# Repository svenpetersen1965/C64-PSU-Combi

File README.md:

# C64-PSU-Combi
A PSU for the Commodore C64 and up to two 1541-II floppy disk drives. It is based on a transformer 
for the 9VAC, which is required in a C64 and a (PCB) external power supply module, which provides
the +5V and +12V for the C64 and the 1541-II floppy disk drives. Depending on the used power supply
module, one of the 1541-II connectors can be replaced with an Amiga connection, which also requires 
-12V. This option has not been tested, since I don't have an Amiga. The PSU combi should be strong 
enough.

This build is for the more experienced, since power supplies can be hazzardous and the involved 
mains voltage is potentially lethal.

Find some info on the required cable making <a href="http://tech.guitarsite.de/cable_making.html">on my website</a>

The power supply has  an open concept and can be configured to taste. It should be planned before 
parts are purchased.

C64 PSU Combi in a Hammond 1411P case

C64 PSU Combi in a Teko 384 case

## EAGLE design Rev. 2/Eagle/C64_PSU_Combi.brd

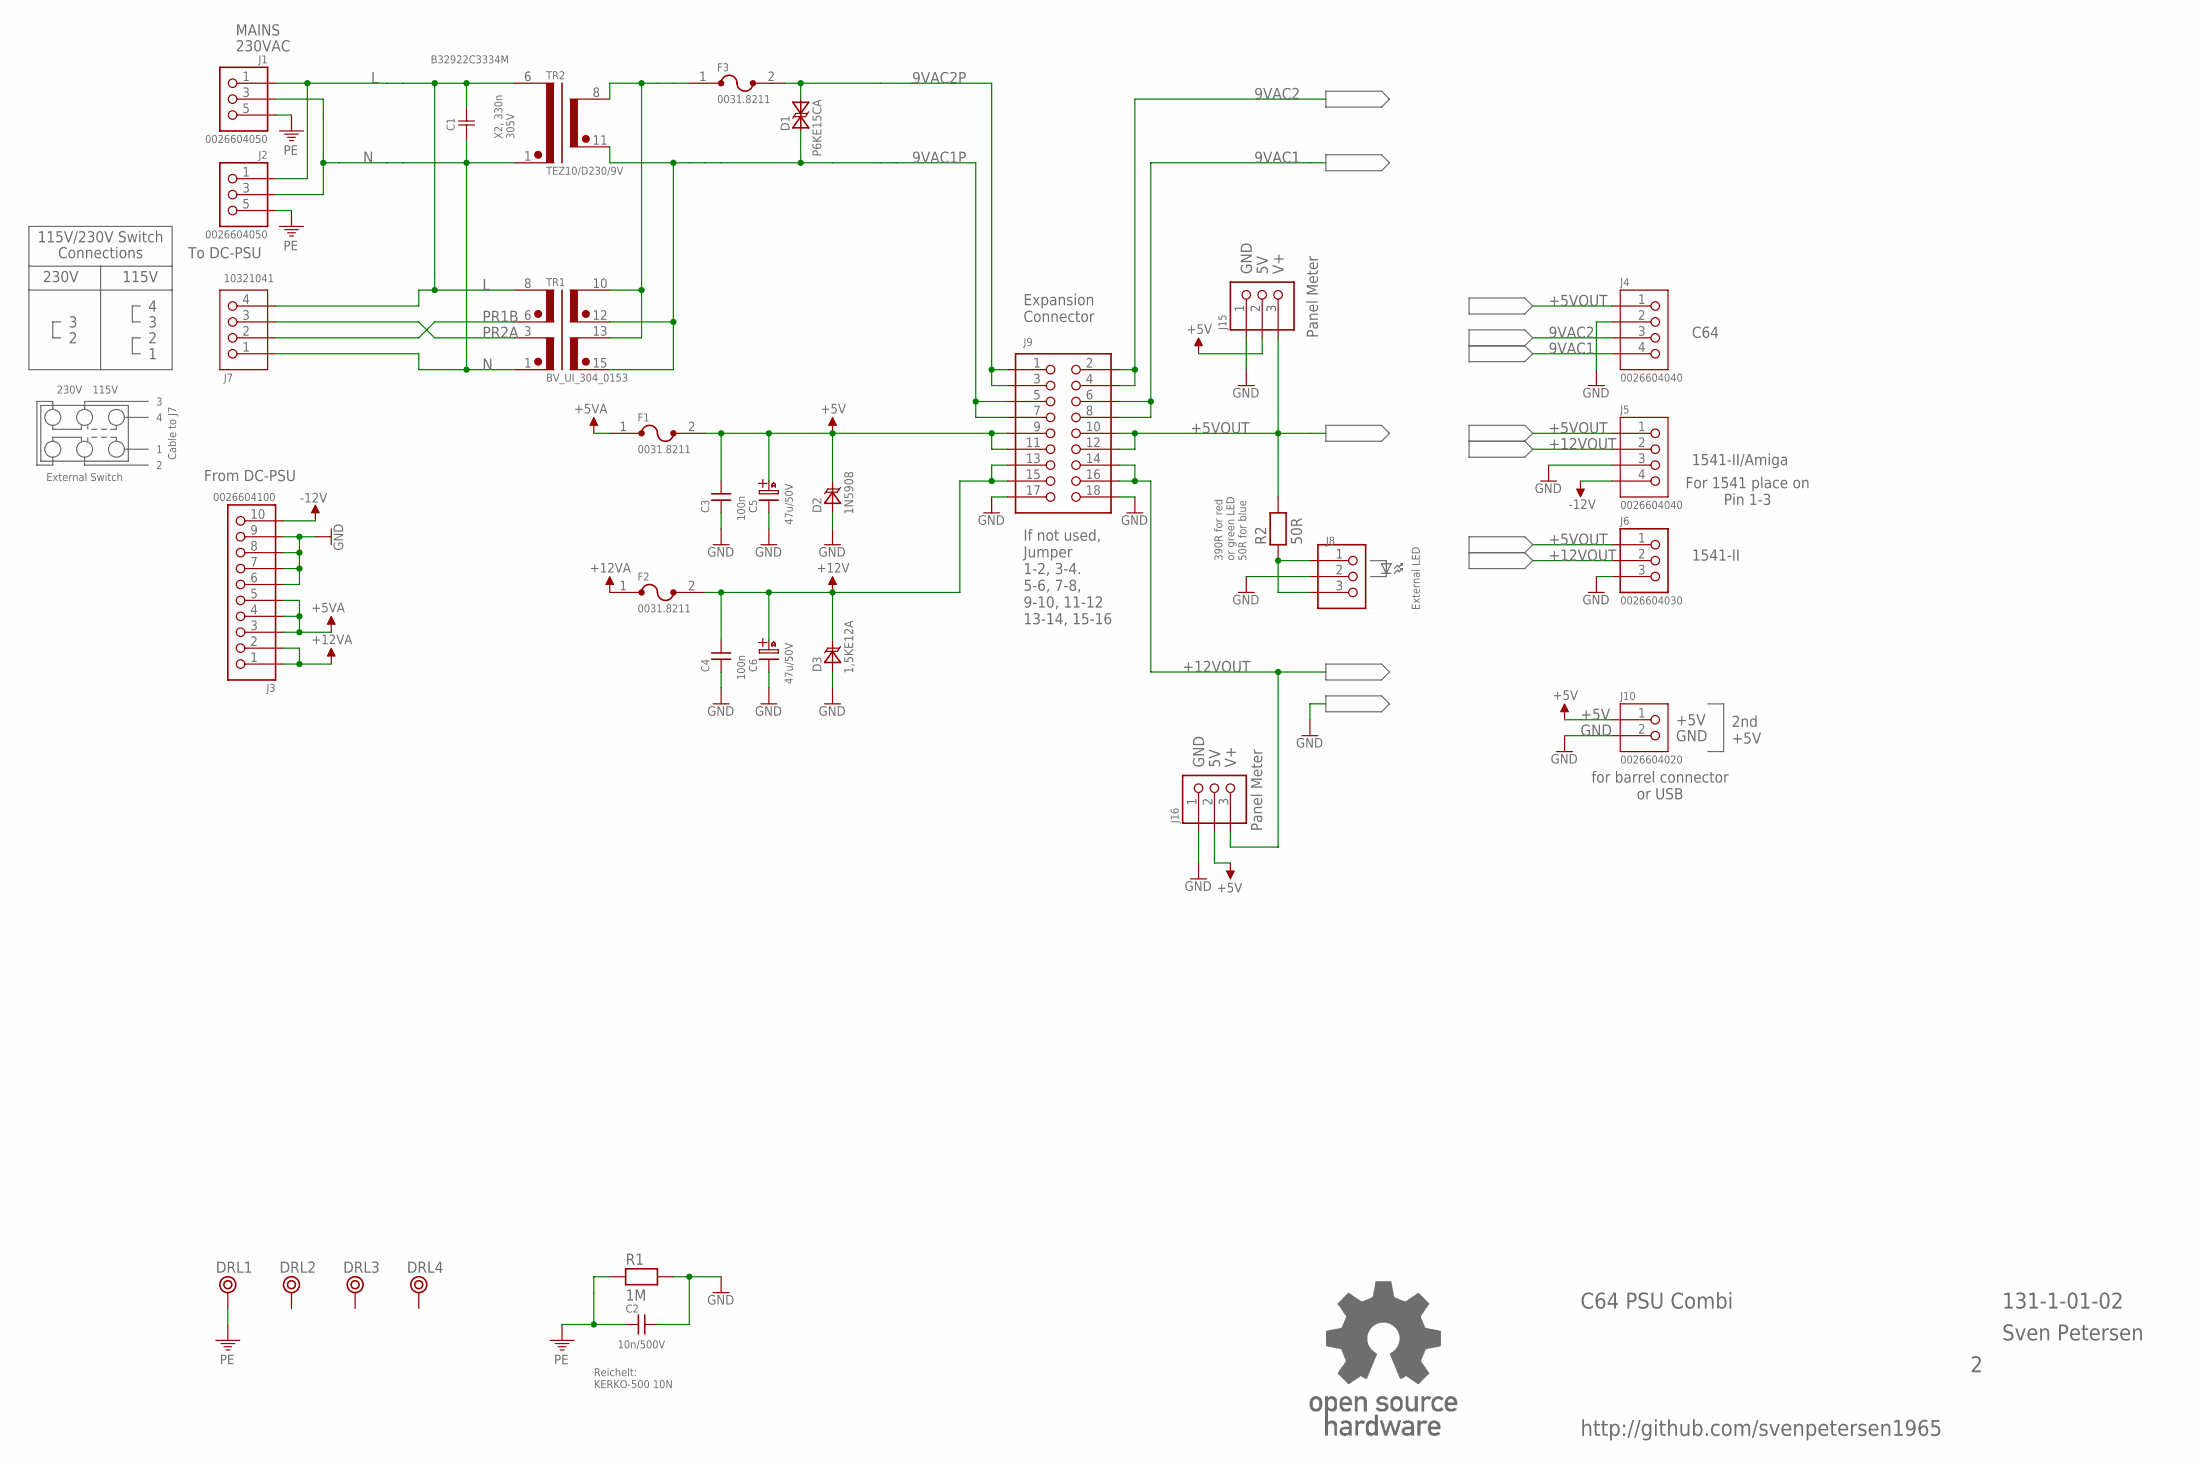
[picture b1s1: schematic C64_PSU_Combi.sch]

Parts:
C1: B32922C3334M; C-18X8-RM15
C2: 10n/500V; C-5
C3, C4: 100n; C-2,5
C5, C6: 47u/50V; C07/2,5
D1: P6KE15CA; CB417NP
D2: 1N5908; CB429
D3: 1,5KE12A; DO-201
DRL1: BOHR3,5OR; BOHR3,5_OHNE_RESTRICT
DRL2, DRL3, DRL4: BOHR3,5
F1, F2, F3: 0031.8211
J1, J2: 0026604050; SPOX_3.96_5P3
J3: 0026604100; SPOX_3.96_10P
J4, J5: 0026604040; SPOX_3.96_4P
J6: 0026604030; SPOX_3.96_3P
J7: 10321041; SPOX_5.08_4P
J8: PINHD-1X3; 1X03
J9: COMBI-9X2P; COMBI-9X2
J10: 0026604020; SPOX_3.96_2P
J15, J16: 6410-3P
R1: 1M; R-10
R2: 50R; R-10
TR1: BV_UI_304_0153; UI30
TR2: TEZ10/D230/9V; TEZ10
U$31: OPEN_SOURCE_HW; OPENHW

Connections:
9VAC1: J4.4, J9.6, J9.8
9VAC1P: D1.A (A1), J9.5, J9.7, TR1.12 (SEC1B), TR1.15 (SEC2B), TR2.11 (SEC12)
9VAC2: J4.3, J9.2, J9.4
9VAC2F: F3.1, TR1.10 (SEC1A), TR1.13 (SEC2A), TR2.8 (SEC11)
9VAC2P: D1.K (A2), F3.2, J9.1, J9.3
+5V: C3.2, C5.A (+), D2.K, F1.2, J9.9, J9.11, J10.1, J15.2, J16.2
+5VA: F1.1, J3.3, J3.4, J3.5
+5VOUT: J4.1, J5.1, J6.1, J9.10, J9.12, J15.3, R2.2
+12V: C4.2, C6.A (+), D3.K, F2.2, J9.13, J9.15
+12VA: F2.1, J3.1, J3.2
+12VOUT: J5.2, J6.2, J9.14, J9.16, J16.3
-12V: J3.10, J5.4
GND: C2.2, C3.1, C4.1, C5.K (-), C6.K (-), D2.A, D3.A, J3.6, J3.7, J3.8, J3.9, J4.2, J5.3, J6.3, J8.2, J9.17, J9.18, J10.2, J15.1, J16.1, R1.2
L: C1.2, J1.1, J2.1, J7.4, TR1.8 (PRI1A), TR2.6 (PRI1)
N: C1.1, J1.3 (2), J2.3 (2), J7.1, TR1.1 (PRI2B), TR2.1 (PRI2)
unnamed: J8.1, J8.3, R2.1
PE: C2.1, DRL1.P$1, J1.5 (3), J2.5 (3), R1.1
PR1B: J7.2, TR1.6 (PRI1B)
PR2A: J7.3, TR1.3 (PRI2A)

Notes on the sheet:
230VAC
X2, 330n 305V
External LED
390R for red or green LED 50R for blue
Reichelt: KERKO-500 10N
Expansion Connector
If not used, Jumper 1-2, 3-4. 5-6, 7-8, 9-10, 11-12 13-14, 15-16
GND
Panel Meter
MAINS
From DC-PSU
C64
1541-II/Amiga
1541-II
C64 PSU Combi
131-1-01-02
Sven Petersen
To DC-PSU
For 1541 place on Pin 1-3
115V/230V Switch
230V
115V
Connections
Cable to J7
External Switch
http://github.com/svenpetersen1965
+5V
2nd +5V
for barrel connector or USB

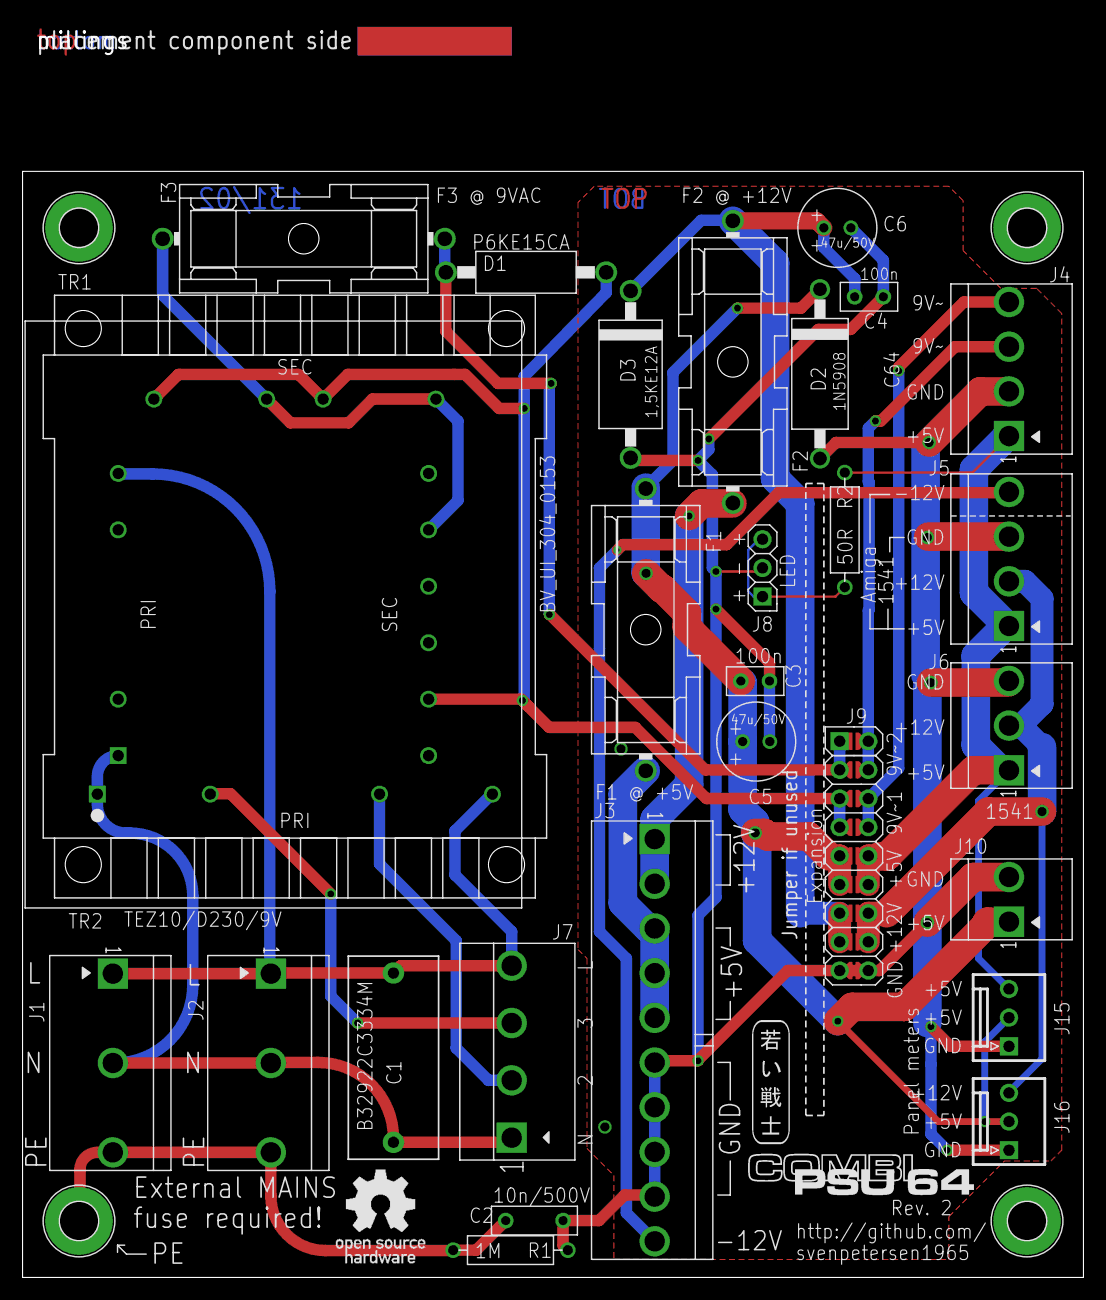
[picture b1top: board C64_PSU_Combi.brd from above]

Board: 2 copper layers, 94.0 x 111.2 mm, 37 parts (0 on the bottom side), 19 nets.

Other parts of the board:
U$43: SVEN_TAG
U$44: PCB-TITLE/
U$45: 2LAYER
U$49: COMBIPSU64

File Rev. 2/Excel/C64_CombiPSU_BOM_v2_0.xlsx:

C64 Combi PSU Rev. 2
Bill of Material Rev. 2.0
Pos. | Qty | Value | Footprint | Ref.-No. | Comment
1 | 1 | 131-2-01-02 | 2 Layer | PCB Rev. 2 | 2 layer, Cu 35µ, HASL, 94.0 x 98.0, 1.6mm FR4
2 | 2 | 22-27-2031 | 6410-3P | J15, J16 | optional (for panel meters): Molex 6410/22-27-2031 (KK, 2.54mm, 3p), e.g. Reich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
3 | 2 | 22-01-3037 |  | (J15), (J16) | crimp housing, optional (for panel meters), Molex. E.g. Reichelt: MOLEX 2201303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
4 | 6 | 08-50-0114 |  | (J15), (J16) | crimp terminal, optional (for panel meters), Molex. E.g. Reichelt: MOLEX 850011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
5 | 1 | 1x3p, 2.54mm | 1X03 | J8 | standard pin header, 2.54mm pitch
6 | 1 | dupont housing, 3p |  | (J8) | ebay, AliExpress or other
7 | 2 | dupont terminals, female |  | (J8) | ebay, AliExpress or other
8 | 1 | LED, blue |  | (J8) | Power LED, blue (R1 is calculated for blue)
9 | 1 | 2x9p, 2.54mm | 2X09 | J9 | standard pin header, 2.54mm pitch
10 | 8 | jumper, 2.54mm |  | (J9) | standard jumper (rated 3A). E.G. Reichelt: JUMPER 2,54 SW, tme.eu: 63429-202LF
11 | 2 or 1 | 26604030 | SPOX_3.96_3P | J6, (J5) | J5 for 1541 option, Molex SPOX, e.G. Reichelt: MOLEX 26604030, tme.eu: MX-26-60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
12 | 2 or 1 | 09503031 |  | (J6), (J5) | crimp housing: Molex. E.g. Reichelt: MOLEX 9503031, tme.eu: MX-2139-3A
13 | 6 or 3 | 08500106 |  | (J6), (J5) | crimp terminal, Molex. E.g. Reichelt: MOLEX 08500106, tme.eu: MX-2478-1-P913L (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
14 | 1 or 2 | 26604040 | SPOX_3.96_4P | J4, (J5) | J5 for Amiga option, Molex SPOX, e.G. Reichelt: MOLEX 26604040, tme.eu: MX-26-6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
15 | 1 or 2 | 09503041 |  | (J4), (J5) | crimp housing: Molex. E.g. Reichelt: MOLEX 9503041, tme.eu: MX-2139-4A
16 | 4 or 8 | 08500106 |  | (J4), (J5) | crimp terminal, Molex. E.g. Reichelt: MOLEX 08500106, tme.eu: MX-2478-1-P913L (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
17 | 2 | 26604050 | SPOX_3.96_5P3 | J1, J2 | Modification: Remove Pin 2 and Pin 4. Molex SPOX, e.G. Reichelt: MOLEX 26604050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
18 | 2 | 09503051 |  | (J1), (J2) | crimp housing: Molex. E.g. Reichelt: MOLEX 9503051, tme.eu: MX-2139-5A
19 | 6 | 08500106 |  | (J1), (J2) | crimp terminal, Molex. E.g. Reichelt: MOLEX 08500106, tme.eu: MX-2478-1-P913L (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
20 | 1 | 26604100 | SPOX_3.96_10P | J3 | Molex SPOX, e.G. Reichelt: MOLEX 26604100, tme.eu: MX-26-60-4100
21 | 1 | 09503101 |  | (J3) | crimp housing: Molex. E.g. Reichelt: MOLEX 9503101, tme.eu: MX-2139-10A
22 | 10 | 08500106 |  | (J3) | crimp terminal, Molex. E.g. Reichelt: MOLEX 08500106, tme.eu: MX-2478-1-P913L (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
23 | 3 | 0031.8211 | 318211 | F1, F2, F3 | Schurter fuse holder (5x20mm). E.g. Reichelt: PL OGN-25, tme.eu: 0031.8211
24 | 1 | 3AT, 5x20mm |  | (F1) | fuse, refer to documentation
25 | 1 | 1.6AT, 5x20mm |  | (F2) | fuse, refer to documentation
26 | 1 | 1.6AT, 5x20mm |  | (F3) | fuse, refer to documentation
27 | 1 | 1,5KE12A | DO-201 | D3 | 12V TVS diode. E.g. ST Micro. E.g. Reichelt: 1,5KE 12A, tme.eu: 1.5KE12A
28 | 2 | 100n | C-2,5 | C3, C4 | Ceramic Cap, 50V, pitch 2.5mm
29 | 1 | 10n/500V | C-5 | C2 | Ceramic Cap, 500V, pitch 5mm, Reichelt: KERKO-500 10N, tme.eu: CCH-10K (=10 pac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
30 | 1 | 1M | R-10 | R1 | Resistor, metal film, 5% or better, 0,6W
31 | 1 | 1N5908 | CB429 | D2 | 5V TVS diode. ST Micro. E.g. Reichelt: 1N 5908, tme.eu: 1N5908
32 | 2 | 47u/50V | C07/2,5 | C5, C6 | el. cap., diameter 7mm, pitch 2.5mm, 105°C, e.G. Reichelt: EB-A 47U 50, tme.eu: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
33 | 1 | 50R | R-10 | R2 | Resistor, metal film, 5% or better, 0,6W, calculated for blue led. For red, gre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
34 | 1 | B32922C3334M | C-18X8-RM15 | C1 | X2-capacitor, 330n, 305V, EPCOS. E.g. Reichelt EPCO B32922C3334, tme.eu: B32922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
35 | 1 | P6KE15CA | CB417NP | D1 | 15V bi-dir TVS diode, ST Micro, e.G. Reichelt: P6KE 15CA, tme.eu: P6KE15CA
36 | 1 | TEZ10/D230/9V | TEZ10 | TR2 | BREVE TUFVASSONS transformer, option 230V only, tme.eu: TEZ10/D/9V
37 | 1 | BV UI 304 0153 | UI30 | TR1 | Hahn transformer, option 115V/230V, tme.eu: BVUI3040153
38 | 1 | 10321041 | SPOX_5.08_4P | J2 | MOLEX, option: 115V/230V switch, tme.eu: MX-5281-04A
39 | 1 | 10013046 |  | (J2) | MOLEX, option: 115V/230V switch., tme.eu: MX-5197-04, Farnell: 2612656 , Mouser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
40 | 4 | 08701031 |  | (J2) | Molex Crimp terminal, option 115V/230V, Farnell: 2060658, rs-online.com: 670-62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
41 | 1 | T22205B436B |  | (J2) | Bulgin, option 115/230V (switch), tme.eu: AE-T22205B
42 | 123cm | AWG21/0.5mm², red |  |  | Cable
43 | 90cm | AWG21/0.5mm², yellow |  |  | Cable
44 | 128cm | AWG21/0.5mm², black |  |  | Cable
45 | 64cm | AWG21/0.5mm², green |  |  | Cable
46 | 56cm | AWG21/0.5mm², blue |  |  | Cable
47 | 56cm | AWG21/0.5mm², brown |  |  | Cable
48 | 34cm | AWG21/0.5mm², green/yellow |  |  | Cable
49 | 10cm | AWG24/0.25mm², red |  |  | Cable
50 | 10cm | AWG24/0.25mm², black |  |  | Cable
49 | 3cm | 2.4/1.2mm |  |  | shrinkable sleve, shrink ration 1:2
50 | 24cm | 3.2/1.6mm |  |  | shrinkable sleve, shrink ration 1:2
50 | 7 | FastOn 6.3x0.8, full iso, red |  |  | crimp connector, e.g. tme.eu 2-520183-2
51 | 7 | Fork connectors, M3, iso, red |  |  | crimp connector, e.g. tme.eu ST-090/R
52 | 1 | DIN jack, 7-way, panel mount |  |  | e.b. tme.eu: DC-109
53 | 2 | DIN jack, 4-way, panel mount |  |  | e.g. tme.eu: MAB4
54 | 1 | Hammond 1411P |  |  | Aluminum case, tme.eu: HM-1411P
55 | 1 | Mounting plate |  |  | Aluminum sheet (99mm x 97mm x 2mm), see drawing: Doc. No. 131-3-01-01
56 | 75mm | 10mm/20mm x 1.5mm |  |  | Aluminum angle profile, see drawing: Doc. No. 131-3-01-01
57 | 8 | M3x10, countersunk |  |  | Screw, DIN 965
58 | 18 | M3, selflocking nut |  |  | DIN 985
59 | 9 | M3, toothed washer |  |  | DIN 6798
60 | 4 | M3/15mm, male/female |  |  | spacer
61 | 10 | M3x10 |  |  | DIN 7985
62 | 10 | M3 washer (3.2mm) |  |  | DIN 125A
63 | 2 | M3x6 |  |  | DIN 7985
64 | 22 | W2.5/L100 |  |  | Cable tie, width 2.5mm, length 100mm, e.g. tme.eu: BMB1025
65 | 1 | RD-50A |  |  | Mean Well DC PSU, e.g. tme.eu: RD-50A
66 | 2 | DIN plugs, 7-way |  |  | e.g. tme.eu MAS70SGR
67 | 4 | DIN plugs, 4 way |  |  | e.g. tme.eu: MAS40
68 | 3.9m | 4xAWG21/0.5mm² |  |  | Cable
69 | 1 | adhesive socket |  |  | for cable ties/cabeling
70 | 1 | 6200.2300 |  |  | Marquardt, appliance connector, tme.eu: 6200.6300
71 | 1 | 1835.3118 |  |  | Marquardt, illuminated mains switch, tme.eu: 1835.3118
72 | 1 | 0026604020 | SPOX_3.96_2P | J10 | Molex KK 396 Header, Vertical, Friction Lock, 2 Circuits
73 | 1 | 09503021 |  | (J10) | KK 3.96mm Crimp Terminal Housing, Friction Ramp, 2 Circuits
74 | 2 | 08500106 |  |  | crimp terminal, Molex. E.g. Reichelt: MOLEX 08500106, tme.eu: MX-2478-1-P913L (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

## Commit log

2020-03-13 Initial upload
2020-03-13 Now with disclaimer
2020-04-22 Rev. 1 released
2020-08-08 Silk Screen Update
2023-03-01 Rev. 2 released
